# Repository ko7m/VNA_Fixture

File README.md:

VNA_Fixture

===========

Single port VNA test fixture for simple networks

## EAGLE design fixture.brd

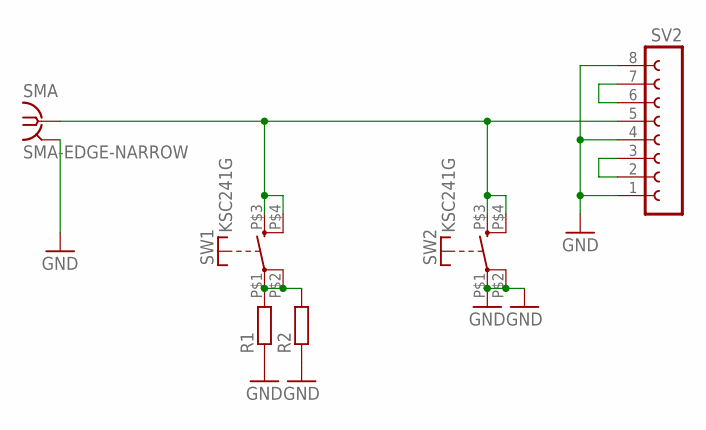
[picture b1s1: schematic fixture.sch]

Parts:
R1, R2: R-EU_M0805; M0805
SMA: SMA-EDGE-NARROW; SMD-EDGE-NARROW
SV2: FE08-1; FE08
SW1, SW2: KSC241G

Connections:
GND: R1.1, R2.1, SMA.G@1 (2), SMA.G@2 (2), SMA.G@3 (2), SMA.G@4 (2), SV2.1, SV2.4, SV2.8, SW2.P$1, SW2.P$2
unnamed: SV2.2, SV2.3
unnamed: R1.2, R2.2, SW1.P$1, SW1.P$2
unnamed: SV2.6, SV2.7
SIG: SMA.1, SV2.5, SW1.P$3 (S), SW1.P$4 (S), SW2.P$3 (S), SW2.P$4 (S)

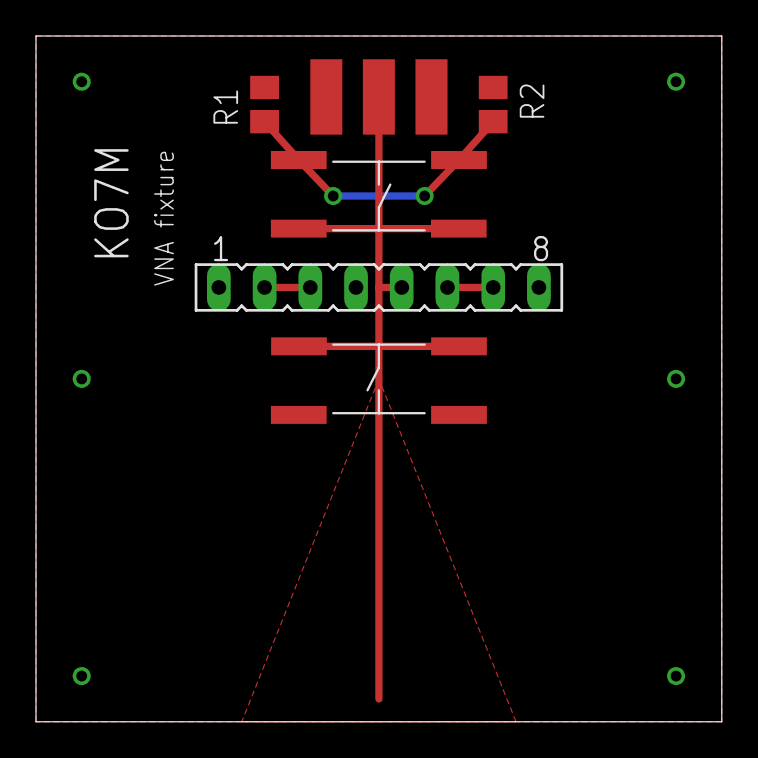
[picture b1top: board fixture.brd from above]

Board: 2 copper layers, 38.1 x 38.1 mm, 6 parts (0 on the bottom side), 5 nets.

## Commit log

2014-11-13 Initial files
2014-11-13 Adding Eagle files
